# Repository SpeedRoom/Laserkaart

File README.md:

# Laserkaart

Code voor de ESP32 van het laserpaneel staat in Laserdinges.

Code voor de ESP32's die de moteren besturen staat in Motordinges.
Deze code is het zelfde voor alle 3 de ESP32's

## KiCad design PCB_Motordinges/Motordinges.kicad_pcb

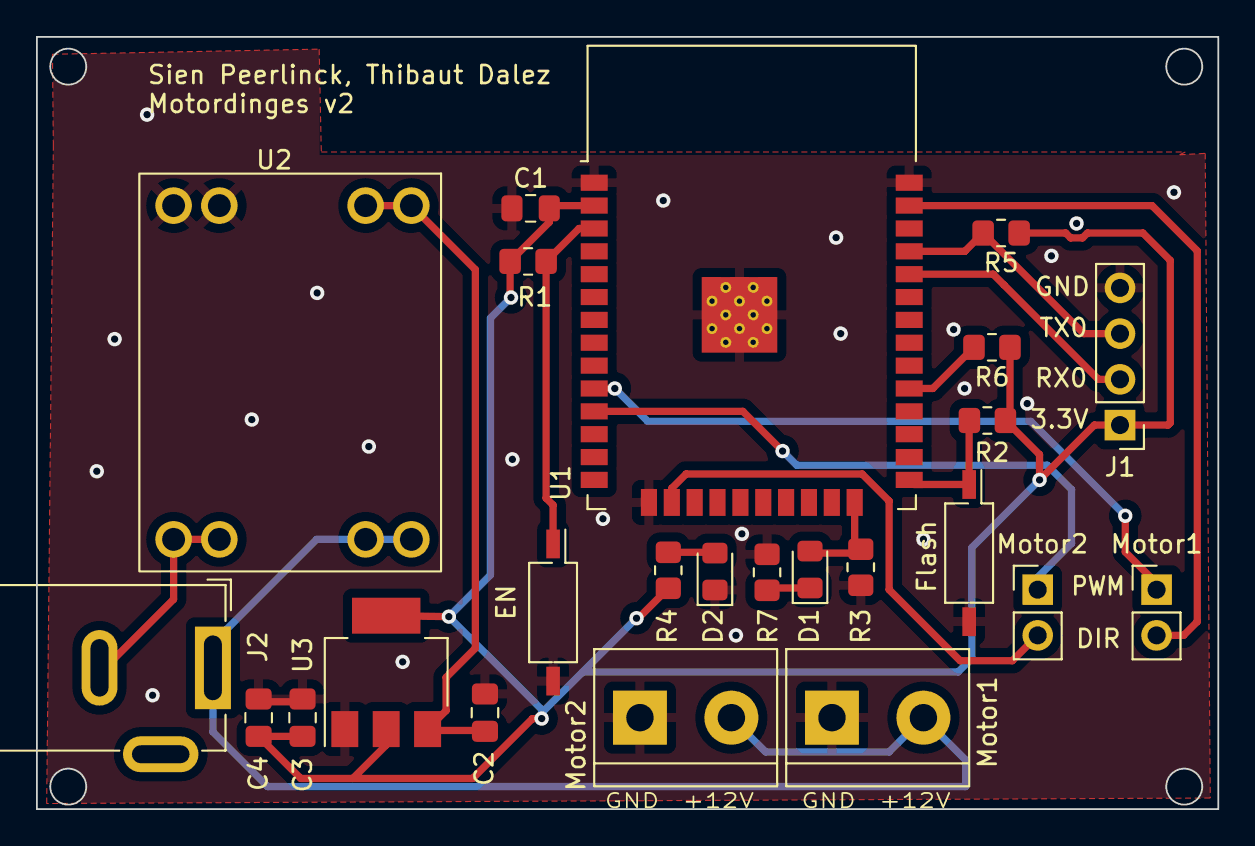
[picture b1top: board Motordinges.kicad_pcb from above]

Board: 2 copper layers, 65.6 x 42.9 mm, 24 parts (0 on the bottom side), 17 nets.

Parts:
C1: 100uF/6.3V; C_0805_2012Metric_Pad1.18x1.45mm_HandSolder
C2, C4: 10uF; C_0805_2012Metric_Pad1.18x1.45mm_HandSolder
C3: 100nF; C_0805_2012Metric_Pad1.18x1.45mm_HandSolder
D1: BLUE; LED_0805_2012Metric_Pad1.15x1.40mm_HandSolder
D2: PWR; LED_0805_2012Metric_Pad1.15x1.40mm_HandSolder
J1: Conn_01x04_Pin; PinHeader_1x04_P2.54mm_Vertical
J2: Barrel_Jack; BarrelJack_GCT_DCJ200-10-A_Horizontal
Motor1, Motor2#2: Conn_01x02_Pin; PinHeader_1x02_P2.54mm_Vertical
Motor1#2, Motor2: Conn_01x02_Pin; TerminalBlock_bornier-2_P5.08mm
R1, R2, R3, R5, R6: 10K; R_0805_2012Metric_Pad1.20x1.40mm_HandSolder
R4, R7: 1K; R_0805_2012Metric_Pad1.20x1.40mm_HandSolder
SW1: EN; SW_DIP_SPSTx01_Slide_Copal_CHS-01B_W7.62mm_P1.27mm
SW2: FLASH; SW_DIP_SPSTx01_Slide_Copal_CHS-01B_W7.62mm_P1.27mm
U1: ESP32-WROOM-32
U2: MP1584; U1584
U3: AMS1117-3.3; SOT-223-3_TabPin2

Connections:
+3.3V: C1.1, C3.2, C4.1, J1.1, R1.1, R2.1, R4.1, R5.1, R6.1, U1.2 (VDD), U3.2 (VO)
/EN: R1.2, SW1.1, U1.3 (EN)
A8: Motor1.1, U1.10 (IO25)
A9: Motor2#2.1, U1.11 (IO26)
GND: C1.2, C2.2, C3.1, C4.2, D2.1 (K), J1.4, Motor1#2.1, Motor2.1, R3.1, R7.2, SW1.2, SW2.2, U1.1 (GND), U1.15 (GND), U1.38 (GND), U1.39 (GND), U2.7 (OUT-), U2.8 (OUT-), U3.1 (GND)
GPIO0: R2.2, SW2.1, U1.25 (IO0)
GPIO2: D1.2 (A), R3.2, U1.24 (IO2)
GPIO5: R6.2, U1.29 (IO5)
GPIO13: Motor2#2.2, U1.16 (IO13)
GPIO23: Motor1.2, U1.37 (IO23)
unnamed: D1.1 (K), R7.1
unnamed: D2.2 (A), R4.2
unnamed: J2.2, U2.1 (IN-), U2.2 (IN-)
unnamed: J2.1, Motor1#2.2, Motor2.2, U2.3 (IN+), U2.4 (IN+)
RX0: J1.2, U1.34 (RXD0/IO3)
TX0: J1.3, R5.2, U1.35 (TXD0/IO1)
VDD: C2.1, U2.5 (OUT+), U2.6 (OUT+), U3.3 (VI)

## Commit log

2023-02-23 laserkaart
2023-02-28 Upload laserdinges en motordinges
2023-03-10 update tweede motor
2023-03-10 platformio
2023-03-10 OTA initialisation
2023-03-28 PCB files
2023-03-28 OTA updated
2023-05-02 random
2023-05-02 pcb_v2
2023-05-08 csv met BOM
2023-05-08 csv met BOM laserdinges
2023-05-08 mislukte testen bij uploaden
2023-05-11 added MQTT
2023-05-11 fixpoging1
2023-05-12 prutsen
2023-05-12 update pcb
2023-05-15 relocation
2023-05-15 finale code
2023-05-16 3d en lasercut files
